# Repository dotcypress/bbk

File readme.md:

# bbk

🚜 Tiny printable robot platform

## License

Licensed under either of

- Apache License, Version 2.0 ([LICENSE-APACHE](LICENSE-APACHE) or
  http://www.apache.org/licenses/LICENSE-2.0)
- MIT license ([LICENSE-MIT](LICENSE-MIT) or http://opensource.org/licenses/MIT)

at your option.

### Contribution

Unless you explicitly state otherwise, any contribution intentionally submitted
for inclusion in the work by you, as defined in the Apache-2.0 license, shall be
dual licensed as above, without any additional terms or conditions.

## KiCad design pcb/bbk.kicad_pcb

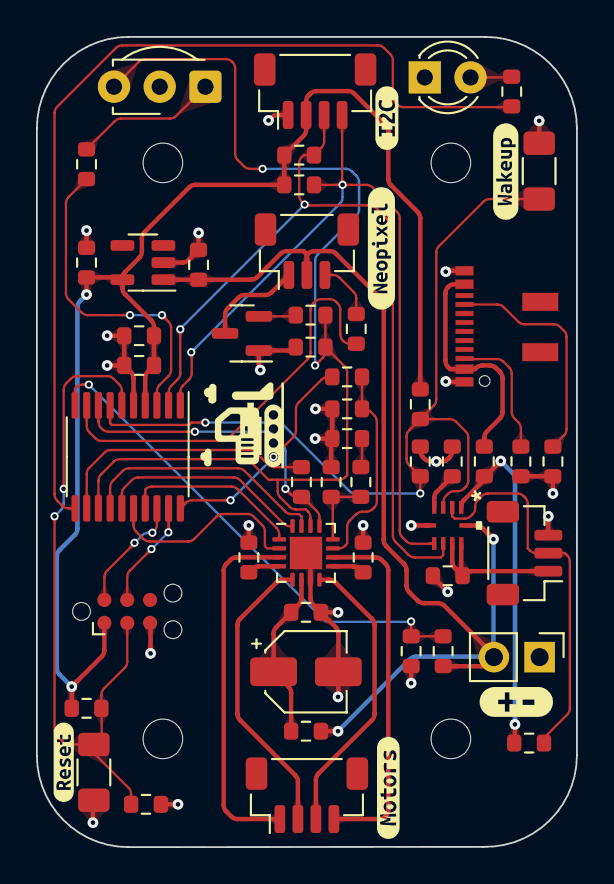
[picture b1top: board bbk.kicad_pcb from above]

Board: 4 copper layers, 30.0 x 45.0 mm, 60 parts (0 on the bottom side), 43 nets.

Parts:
C1, C3, C4, C6, C8, C9: 10uF; R_0603_1608Metric
C2, C5, C7, C10: 100nF; R_0603_1608Metric
C11: 22uF; CP_Elec_4x4.5
C12: 22nF; R_0603_1608Metric
D1: TSAL4400; LED_D3.0mm_IRBlack
F1: Polyfuse; R_0603_1608Metric
FB1: FerriteBead; R_0603_1608Metric
H1, H2, H3, H4: MountingHole; MountingHole_2.2mm_M2
J1: USB_C_Receptacle_USB2.0; USB_C_Receptacle_JAE_DX07S016JA3R1500
J2: Neopixel; JST_SH_BM03B-SRSS-TB_1x03-1MP_P1.00mm_Vertical
J3: ExtPower; PinHeader_1x02_P2.54mm_Vertical
J4: TagConnect; Tag-Connect_TC2030-IDC-NL_2x03_P1.27mm_Vertical
J5: Li-Ion; JST_SH_BM03B-SRSS-TB_1x03-1MP_P1.00mm_Vertical
J6: I2C; JST_SH_BM04B-SRSS-TB_1x04-1MP_P1.00mm_Vertical
J7: Motors; JST_SH_BM04B-SRSS-TB_1x04-1MP_P1.00mm_Vertical
Q1: PMV15ENEA; SOT-23
R1, R6, R7, R9, R12, R20: 10K; R_0603_1608Metric
R2, R5, R10: 190R; R_0603_1608Metric
R3, R4, R13, R18, R19: 5.1K; R_0603_1608Metric
R8: 20K; R_0603_1608Metric
R11: 330R; R_0603_1608Metric
R14: 47K; R_0603_1608Metric
R15: 1K; R_0603_1608Metric
R16, R17: 2R; R_0603_1608Metric
SW1: Reset; R_1206_3216Metric_Pad1.30x1.75mm_HandSolder
SW2: Wakeup; R_1206_3216Metric_Pad1.30x1.75mm_HandSolder
U1: STM32G0xxFx; TSSOP-20_4.4x6.5mm_P0.65mm
U2: MP2667GG-xxxx-Z
U3: TSOP93338; Vishay_MINICAST-3Pin
U4: AP7370-33W5-7; TSOT-23-5
U5: STSPIN240; VQFN-16-1EP_3x3mm_P0.5mm_EP1.8x1.8mm
kibuzzard-6354BB14: G***; kibuzzard-6354BB14
kibuzzard-6354BBA3: G***; kibuzzard-6354BBA3
kibuzzard-6354BC68: G***; kibuzzard-6354BC68
kibuzzard-6354BC97: G***; kibuzzard-6354BC97
kibuzzard-6354BCC6: G***; kibuzzard-6354BCC6
kibuzzard-6354BCF7: G***; kibuzzard-6354BCF7

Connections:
+3.3V: C1.1, C2.1, C8.1, J4.1 (Vdd), J6.2, R6.1, R9.1, R18.2, R19.2, U1.4 (VDD), U4.5 (VOUT)
/ADC_BAT: R7.2, R8.1, U1.10 (PA3)
/BAT+: C4.2, J5.1, U2.8 (BATT), U2.9 (BATT)
/CHARGER_VDD: C3.2, U2.4 (VDD)
/CHARGER_VIN: F1.2, R20.2, U2.1 (IN)
/DRIVE_EN: R12.1, U1.12 (PA5)
/DRIVE_REF: R13.2, U1.20 (PB3/PB4/PB5/PB6)
/FAULT: R12.2, U1.8 (PA1), U5.13 (EN/FLT)
/I2C_INT: C7.1, R9.2, SW2.1, U1.7 (PA0), U2.3 (INT)
/I2C_SCL: J6.4, R19.1, U1.1 (PB7/PB8), U2.6 (SCL)
/I2C_SDA: J6.3, R18.1, U1.2 (PB9/PC14/OSC_IN), U2.7 (SDA)
/IR_RX: R10.1, U1.3 (PC15/OSC_OUT)
/IR_TX: R11.2, U1.11 (PA4)
/MOTOR_A1: J7.1, U5.3 (OUTA1)
/MOTOR_A2: J7.2, U5.5 (OUTA2)
/MOTOR_A_SENSE: R16.1, U5.4 (SENSEA)
/MOTOR_B1: J7.4, U5.10 (OUTB1)
/MOTOR_B2: J7.3, U5.8 (OUTB2)
/MOTOR_B_SENSE: R17.1, U5.9 (SENSEB)
/MOTOR_VSS: C10.1, C11.1, FB1.2, U5.6 (VS)
/NEOPIXEL: R5.2, U1.9 (PA2)
/NEOPIXEL_GND: J2.1, Q1.3 (D)
/NTC: J5.2, R20.1, U2.2 (NTC)
/PHASE_A: U1.17 (PA12[PA10]), U5.1 (PHA)
/PHASE_B: U1.14 (PA7), U5.15 (PHB)
/PWM_A: U1.16 (PA11[PA9]), U5.2 (PWMA)
/PWM_B: U1.15 (PB0/PB1/PB2/PA5), U5.16 (PWMB)
/STANDBY: R1.1, R2.2, U1.13 (PA6), U3.3 (Vs), U5.14 (STBY/RESET)
/V_USB: F1.1, J1.A4 (VBUS), J1.A9 (VBUS)
/nRST: C5.1, J4.3 (nRST), R6.2, SW1.1, U1.6 (NRST)
GND: C1.2, C2.2, C3.1, C4.1, C5.2, C6.2, C7.2, C8.2, C9.2, C10.2, C11.2, C12.2, D1.1 (K), J1.A1 (GND), J1.A12 (GND), J3.1, J4.5 (GND), J5.3, J6.1, Q1.1 (S), R1.2, R3.2, R4.2, R8.2, R15.1, R16.2, R17.2, SW1.2, SW2.2, U1.5 (VSS), U2.5 (GND), U3.2 (GND), U4.2 (GND), U5.7 (GND), U5.17 (EPAD)
unnamed: C12.1, R14.1
unnamed: D1.2 (A), R11.1
unnamed: J1.A5 (CC1), R3.1
unnamed: J1.B5 (CC2), R4.1
unnamed: J2.3, R5.1
unnamed: J4.4 (SWDCLK), U1.19 (PA14/PA15/BOOT)
unnamed: J4.2 (SWDIO), U1.18 (PA13)
unnamed: Q1.2 (G), R2.1
unnamed: R10.2, U3.1 (OUT)
unnamed: C9.1, R13.1, U5.11 (REF)
unnamed: R14.2, R15.2, U5.12 (TOFF)
VBUS: C6.1, FB1.1, J2.2, J3.2, R7.1, U2.10 (SYS), U4.1 (VIN)

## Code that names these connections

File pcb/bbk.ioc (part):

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Mcu.Name=STM32G030F6Px
Mcu.Package=TSSOP20
Mcu.UserName=STM32G030F6Px
PA0.GPIOParameters=GPIO_Label
PA0.GPIO_Label=I2C_INT
PA0.Mode=SYS_WakeUp0
PA0.Signal=SYS_WKUP1
PA1.GPIOParameters=GPIO_Label
PA1.GPIO_Label=STBY
PA1.Signal=GPIO_Output
PA11\ [PA9].GPIOParameters=GPIO_Label
PA11\ [PA9].GPIO_Label=PWM_A
PA11\ [PA9].Signal=S_TIM1_CH4
PA12\ [PA10].GPIOParameters=GPIO_Label
PA12\ [PA10].GPIO_Label=PHASE_A
PA12\ [PA10].Signal=GPIO_Output
PA13.Mode=Serial_Wire
PA13.Signal=SYS_SWDIO
PA14-BOOT0.Mode=Serial_Wire
PA14-BOOT0.Signal=SYS_SWCLK
PA14-BOOT0__PA15.StandardMode=true
PA2.GPIOParameters=GPIO_Label
PA2.GPIO_Label=NEOPIXEL
PA2.Signal=SPI1_MOSI
PA3.GPIOParameters=GPIO_Label
PA3.GPIO_Label=ADC_BAT
PA3.Mode=IN3
PA3.Signal=ADC1_IN3
PA4.GPIOParameters=GPIO_Label
PA4.GPIO_Label=IR_TX
PA4.Signal=S_TIM14_CH1
PA5.GPIOParameters=GPIO_Label
PA5.GPIO_Label=MOTOR_EN
PA5.Signal=GPIO_Output
PA6.GPIOParameters=GPIO_Label
PA6.GPIO_Label=MOTOR_FAULT
PA6.Signal=GPIO_Output
PA7.GPIOParameters=GPIO_Label
PA7.GPIO_Label=PHASE_B
PA7.Signal=GPIO_Output
PA8.GPIOParameters=GPIO_Label
PA8.GPIO_Label=PWM_B
PA8.Signal=S_TIM1_CH1
PB0__PB1__PB2__PA8.StandardMode=true
PB3__PB4__PB5__PB6.StandardMode=true
PB6.GPIOParameters=GPIO_Label
PB6.GPIO_Label=MOTOR_REF
PB6.Mode=Output Compare1 CH1N
PB6.Signal=TIM16_CH1N
PB7__PB8.StandardMode=true
PB8.Mode=I2C
PB8.Signal=I2C1_SCL
PB9.Mode=I2C
PB9.Signal=I2C1_SDA
PC14-OSC32_IN\ (PC14)__PB9.StandardMode=true
PC15-OSC32_OUT\ (PC15).GPIOParameters=GPIO_Label
PC15-OSC32_OUT\ (PC15).GPIO_Label=IR_RX
PC15-OSC32_OUT\ (PC15).Signal=GPIO_Input
RCC.HSE_VALUE=8000000
RCC.SYSCLKFreq_VALUE=16000000
board=custom

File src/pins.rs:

use crate::hal::gpio::{gpioa::*, gpiob::*, gpioc::*};
use hal::gpio::*;
use hal::prelude::*;
use hal::rcc::Rcc;
use hal::stm32::*;
use crate::*;

// Qwiic I2C
pub type I2cClk = PB8<Output<OpenDrain>>;
pub type I2cSda = PB9<Output<OpenDrain>>;

// Infared
pub type IrTx = PA4<DefaultMode>;
pub type IrRx = PC15<Input<Floating>>;

// Neopixel
pub type Neopixel = PA2<DefaultMode>;

// Power management
pub type Standby = PA6<Output<PushPull>>;
pub type BatterySense = PA3<DefaultMode>;

// Motor control
pub type MotorDriverTork = PB6<DefaultMode>;
pub type MotorDriverEnable = PA5<Output<PushPull>>;
pub type MotorDriverFault = PA1<Input<Floating>>;
pub type MotorAPwm = PA11<DefaultMode>;
pub type MotorBPwm = PA8<DefaultMode>;
pub type MotorAPhase = PA12<Output<PushPull>>;
pub type MotorBPhase = PA7<Output<PushPull>>;

// Buttons
pub type Wakeup = PA0<Input<Floating>>;

// SWD
pub type SwdIo = PA13<DefaultMode>;
pub type SwdClk = PA14<DefaultMode>;

pub struct Pins {
    // Qwiic I2C
    pub i2c_clk: I2cClk,
    pub i2c_sda: I2cSda,

    // Infared
    pub ir_tx: IrTx,
    pub ir_rx: IrRx,

    // Neopixel
    pub neopixel: Neopixel,

    // Power management
    pub standby: Standby,
    pub battery_sense: BatterySense,

    // Motor control
    pub motor_driver_tork: MotorDriverTork,
    pub motor_driver_enable: MotorDriverEnable,
    pub motor_driver_fault: MotorDriverFault,
    pub motor_a_pwm: MotorAPwm,
    pub motor_b_pwm: MotorBPwm,
    pub motor_a_phase: MotorAPhase,
    pub motor_b_phase: MotorBPhase,

    // Buttons
    pub wakeup_button: Wakeup,

    // SWD
    pub swd_io: SwdIo,
    pub swd_clk: SwdClk,
}

impl Pins {
    pub fn new(gpioa: GPIOA, gpiob: GPIOB, gpioc: GPIOC, rcc: &mut Rcc) -> Self {
        let port_a = gpioa.split(rcc);
        let port_b = gpiob.split(rcc);
        let port_c = gpioc.split(rcc);

        Self {
            // Qwiic I2C
            i2c_clk: port_b.pb8.into_open_drain_output_in_state(PinState::High),
            i2c_sda: port_b.pb9.into_open_drain_output_in_state(PinState::High),

            // Infared
            ir_tx: port_a.pa4,
            ir_rx: port_c.pc15.into(),

            // Neopixel
            neopixel: port_a.pa2,

            // Power management
            standby: port_a.pa6.into(),
            battery_sense: port_a.pa3,

            // Motor control
            motor_driver_tork: port_b.pb6,
            motor_driver_enable: port_a.pa5.into(),
            motor_driver_fault: port_a.pa1.into(),
            motor_a_pwm: port_a.pa11,
            motor_b_pwm: port_a.pa8,
            motor_a_phase: port_a.pa12.into(),
            motor_b_phase: port_a.pa7.into(),

            // SWD
            swd_io: port_a.pa13,
            swd_clk: port_a.pa14,

            // Buttons
            wakeup_button: port_a.pa0.into(),
        }
    }
}

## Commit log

2022-10-24 init
2022-10-24 add example
2022-11-11 convert to app
2022-12-09 cleanup
2022-12-11 stream artifact

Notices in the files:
parts and their libraries:
Copyright 2021 Accelerated Designs. All rights reserved.
